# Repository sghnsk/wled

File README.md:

# wled
плата и корпус для wled на esp-12 с минимальной обвязкой

документация проекта wled: https://kno.wled.ge/

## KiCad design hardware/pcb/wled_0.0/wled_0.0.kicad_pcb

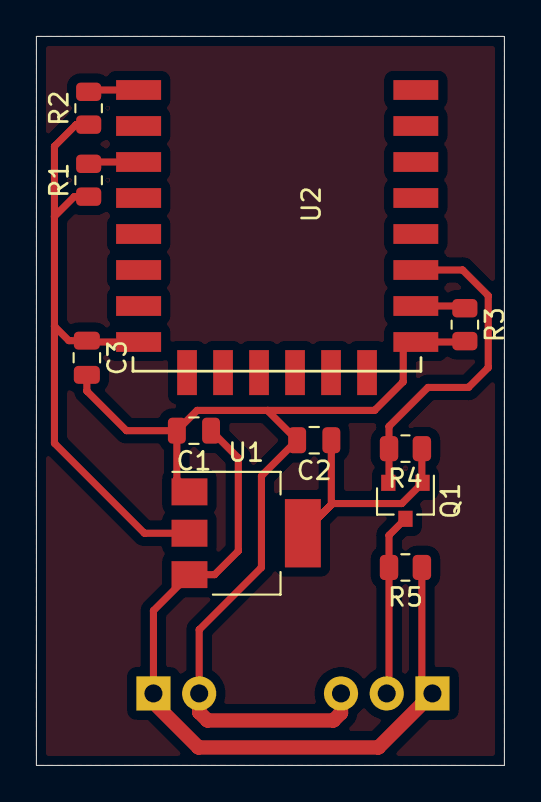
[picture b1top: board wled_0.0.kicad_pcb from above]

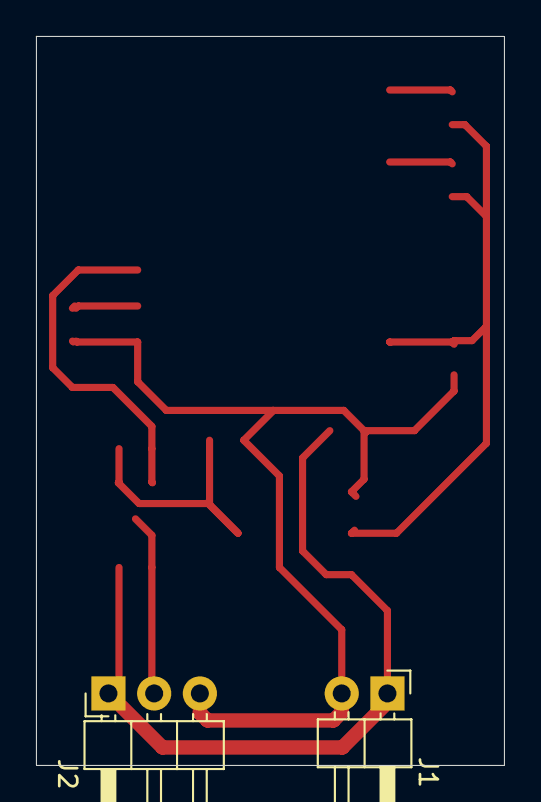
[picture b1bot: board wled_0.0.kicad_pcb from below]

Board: 2 copper layers, 26.0 x 40.5 mm, 13 parts (2 on the bottom side), 8 nets.

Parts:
C1, C2, C3: 100; C_0805_2012Metric
J1: Conn_01x02_Female; PinHeader_1x02_P2.54mm_Horizontal
J2: Conn_01x03_Female; PinHeader_1x03_P2.54mm_Horizontal
Q1: BSS138; SOT-23
R1, R2, R3: 4k7; R_0805_2012Metric
R4, R5: 10k; R_0805_2012Metric
U1: AMS1117-3.3; SOT-223-3_TabPin2
U2: ESP-12; ESP-12E_SMD

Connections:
+5V: C1.1, J1.1, J2.1, R5.1, U1.3
GND: C1.2, C2.2, C3.2, J1.2, J2.3, R3.2, U1.1, U2.9
unnamed: C2.1, C3.1, Q1.1, R1.1, R2.1, R4.1, U1.2, U2.8
unnamed: J2.2, Q1.3, R5.2
unnamed: Q1.2, R4.2, U2.11
unnamed: R1.2, U2.3
unnamed: R2.2, U2.1
unnamed: R3.1, U2.10

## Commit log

2023-01-04 первй вариант платы
2023-01-06 заменил пути до библиотек с абсолютных
2023-01-06 увеличил размер переходных отверстий с 0.8 до 0.9
2023-01-06 добавил readme
2023-01-11 поменял разъемы с вертикальных на горизонтальные
    + перенес на другую сторону(как было запаяно на тестовых платах)
2023-01-11 попытка использовать переменные kicad во freecad >_<
2023-01-12 заменил 3d модельку esp-12 на более адекватную
2023-01-12 первый вариант днища
2023-01-12 корпус без надписей
2023-01-12 увеличил зазор между крушкой и нижней частью в области разъемов
2023-01-12 добавил текст на верхнюю крышку
2023-01-12 Увеличил текст надписей к разъему
    - после печати ничего не разобрать
2023-01-12 правки в крышке, чтобы не болталась плата
2023-01-12 Итоговые stl-ки
    - для этого этапа
2023-01-15 Добавил отдлельно текст для первого слоя крышки
    - stl-ки в пример - для печати разными цветами:
    1. добавить Captions.stl
    2. добавить Top.stl
    3. разместить в слайсере обе модели, чтобы текст совпадал
    4. нарезать
    5. сохранить в файл
2023-01-15 пример итогового файла с gcode
2023-02-04 доабвил фотки и скрины
2023-02-04 прописал субмодуль нормально
2023-02-14 правки в схеие и плате:
    - заменил значения резисторов с 4к7 на 10к
    - перенес некоторые дорожки дальше от края, увеличил размер площадок под сверловку
